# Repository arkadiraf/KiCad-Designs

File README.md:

# KiCad-Designs
KiCad Design Projects

| Project | Description |
|---|---|
| [Pico_Alvik_Adapter](Pico_Alvik_Adapter/) | Raspberry Pi Pico W carrier in Arduino Nano form factor, replaces the Nano ESP32 in the Arduino Alvik robot |
| [Drone_1S_Pico2W](Drone_1S_Pico2W/) | 1S toothpick drone: 2 mm PCB frame / power board (from the OpenSCAD 1S_PiZero frame) and a Pico 2 W flight-controller module. Stage 1: bare boards |
| [PicoBalancer](PicoBalancer/) | Two-wheel self-balancing robot: Pico W / Pico 2 W on sockets, 2 x 18650 (1S2P), BNO086, 2 x MP6550, BQ25606 USB-C charger, TPS61235P 5.1 V boost. Stage 0: outline, datasheets, BOM, design doc |

| [Libraries](Libraries/) | Shared KiCad symbols and footprints for reuse across designs (KD_Power: BQ25606, TPS22997, TPS22810DBV, TPS61235P; KD_Sensors: BMI088, BMP388; KD_Modules: Pico 2 W; KD_Connectors: Bitcraze deck socket; KD_Mechanical: NPTH mounting holes) |

## Ordering (all projects)

One Digi-Key order covers every board: `python Orders/combined_order.py <cart.xlsx> [boards=5]` reads each project's
`fabrication/BOM_DigiKey.csv` (and the Pico_Alvik_Adapter parts list), multiplies by the board count and checks the
cart export, writing `Combined_DigiKey_order.xlsx` next to it (need per project, cart quantity, OK / EXTRA / SHORT /
MISSING / not in any BOM, lines to add, parts bought elsewhere). Order of 28 Nov 2026 (5 of each board, Pico 2 W / Pico W from Mouser): [Orders/2026-11-28/](Orders/2026-11-28/).
Stock passives (0603 R / C sample book, 0805 LEDs) for all boards: `python Orders/stock_passives.py [boards=5]` ->
`Stock_passives.xlsx` (checklist with a Have column) and `Stock_passives.md`.

## Design rules (all projects)

* **Passives:** chip resistors and capacitors are **0603**. Bulk capacitors (10 µF and up, or where the
  voltage rating needs a bigger case) are **0805 or 1206**. No 0402 or smaller: the boards are
  hand-assembled. Exceptions (e.g. a current-sense or power resistor in a larger case) must be
  stated next to the part in the project's `design.py`.
* **LEDs:** 0805 (`LED_SMD:LED_0805_2012Metric`). `Drone_1S_Pico2W/tools/check_bom.py`
  enforces this rule. Copy it into new projects.
* **Shared parts:** custom symbols and footprints go in [Libraries](Libraries/), not project-local
  libraries, so later designs can reuse them.

Workflow for new projects (design-as-code generators, checks, manufacturing outputs): see [AGENTS.md](AGENTS.md).

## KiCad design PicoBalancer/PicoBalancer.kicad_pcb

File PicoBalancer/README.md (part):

# PicoBalancer: two-wheel self-balancing robot board

One 60 × 200 × 1.6 mm PCB for a two-wheel balancing robot:
* **MCU:** Raspberry Pi Pico W (RP2040) on 2 × 20 female sockets, upgradable to a Pico 2 W (RP2350) with no board change.
* **Cells:** plain 2 × 18650 (no protection PCB) in parallel (1S2P) in Keystone 1042 holders (not polarized, Digi-Key 36-1042-ND), or the polarized 1042P on the same footprint. Each cell has its own reverse-polarity FET.
* **IMU:** BNO086 on SPI1.
* **Motors:** 2 × MP6550 H-bridges for Pololu #3072 micro metal gearmotors (30:1 HPCB 6V, extended shaft), each with a Pololu 4761 magnetic encoder on one JST-SH 6-pin connector. ISET 4.3 k caps each motor at 1.16 A.
* **Power:** the blocks are reused from [Drone_1S_Pico2W](../Drone_1S_Pico2W/): BQ25606 USB-C charger (vertical GCT USB4235), TPS22810 Pico switch with UVLO, TPS61235P 5.1 V boost.

**Design document:** [docs/PicoBalancer_Hardware_Design.pdf](docs/PicoBalancer_Hardware_Design.pdf), a PDF export of the shared
design doc (block diagram, circuits, pin map, mechanics, parts list, open decisions).
**PCB order:** [fabrication/PicoBalancer_OSHPark.zip](fabrication/PicoBalancer_OSHPark.zip) (OSH Park 2-layer). See [Fabrication](#fabrication-osh-park-stage-4).
**BOM:**
* [fabrication/BOM.md](fabrication/BOM.md): every line.
* [fabrication/BOM_DigiKey.csv](fabrication/BOM_DigiKey.csv): distributor upload. Digi-Key or Mouser, whichever has stock.
* [fabrication/BOM_stock.md](fabrication/BOM_stock.md): 0603 R/C and 0805 LEDs from stock.
* [fabrication/BOM_to_source.md](fabrication/BOM_to_source.md): lines with no distributor number yet.

**Datasheets and verification:** [Materials/bom_datasheets/README.md](Materials/bom_datasheets/README.md).
**Order check:** `python tools/verify_order.py fabrication/DigiKey_order_2026-11-27T093456.xlsx 5` compares the Digi-Key cart with the BOM. Result for the 27 Nov cart (093456): ORDER OK for 5 boards. The Pico WH comes from Mouser / Piitel. Two cart lines are Pico_Alvik_Adapter parts.

## Status: stage 4, ready to order (rev 0.1)

| Stage | Content | State |
|---|---|---|
| 0 | Folder, datasheets, outline + holes from the DXF (checked against Fusion), placement guides, BOM, design doc | **done** |
| 1 | Decisions closed (motor, cells, TS fixed, UVLO option, placement); follow-up: BAT fuse | done |
| 2 | Netlist in `design.py`, KD symbols/footprints (BNO086, MP6550, Pico socket, 1042, USB4235, slide switch, 1812L, wire pads), schematic | **done** |
| 3 | Placement, silkscreen, routing (2 layers): DRC 0 violations, 0 unconnected | **done** |
| 4 | Final review, OSH Park fab outputs (Gerbers, drill, top stencil, positions) | **done** |

## Mechanics

Sources: `Materials/extracted/PicoBalancer_PCB.dxf` and the Fusion 360 model `PicoBalancer_V01 v2`. The model was
read only, over its local MCP server, and **must not be changed without approval.**

Board coordinates: origin at the board centre, x right, y down, viewed from the holder side. The wheel end is at +y.
Fusion: `y_kicad = 121 - y_fusion`.

| Item | Position (mm) |
|---|---|
| Outline | 60 × 200 |
| Holes | 6 × Ø2.65 NPTH (M2.5) at x ±26, y −96 / 0 / +96, 8 × 8 squares from the DXF and Ø7.5 mm head keep-out marks; 2 clamp holes at (0, −61) / (0, −81) (`KD_Mechanical:MountingHole_2.65mm_NPTH`) |
| BT1 / BT2 (1042, alt. 1042P) | centres (±19.675, −49.975): outer walls on the board edges, top end 11.5 mm from the top edge, + contact at the top end (USB side), − spring toward the board centre; pads ≥ 7.46 × 6.47 mm, ≥ 86.80 mm overall, holes Ø3.45 / Ø2.39 mm |
| Channel between holders | x ±8.65, y −93.5…−6.9: vertical USB-C at the top, BQ25606 charger below, two battery-clamp holes in the middle (positions to come from Fusion) |
| Pico | centred, x ±10.5, y 33…84 (antenna end 2.4 mm above the IMU), micro-USB up |
| IMU | centre bottom, about (0, 89): nearest the wheel axle |
| J7 / J8 motor wire pads | bottom corners, left / right, with U3 / U4 drivers above; motor cables soldered directly |

Fusion findings, reported but not changed:
* The 1042P locating pegs pass through the PCB body.
* The PCB body has no holes for those pegs.

## Placement review in Fusion 360 (stage 0b)

`tools/fusion/build_review.py` builds a `PCB_Review` component in the Fusion model (user permission, 27 Nov 2026) from
`design.py`. It contains a 60 × 200 mm board with all holes and one sized block per part (`REVIEW_PARTS`). It also moves
the two holder models to `BT_POS`. The original `PCB` body is hidden. Rerun it after changing `design.py`:

```sh
cd tools/fusion
python build_review.py                 # needs Fusion running with the PicoBalancer model open (MCP server on :27182)
python fusion_mcp.py view_top.py && python screenshot.py ../../docs/fusion_review_top.png 900 1500
```

* **Bolt keep-out:** Ø7.5 mm circle marked at each M2.5 hole (5 mm head).
* **Holder position:** `HOLDER_TOP_OFFSET` is the distance from the PCB top edge to the housing top end: 11.5 mm (confirmed 27 Nov 2026, also the minimum for the keep-out).
* **Battery clamp:** holes at (0, −61) and (0, −81), with the cover pillar (x ±5, y −86…−56) kept free of parts. The charger sits below the pillar and the USB-C above it.
* **Holder joints:**
  * The left holder is positioned through the offsets of the model's rigid joint "Rigid 6".
  * The right holder is a mirrored copy in the model, so its locating bosses are on the wrong diagonal. The review PCB holes follow a real holder.

## Key electrical choices (details in the design doc)

* **Reverse-polarity protection, one channel per cell** (Q1–Q4, R28–R33). A shared FET cannot protect parallel cells.
  * Each holder's + contact goes to BAT through its own P-FET (DMP2008UFG, 9.8 mΩ max at −2.5 V).
  * A DMG2302U turns that P-FET on only when its own cell is the right way round.
  * A reversed cell is blocked, an empty holder's contacts are dead, and charging still works through the P-FET channel.
  * This makes the non-polarized Keystone 1042 safe to use.
* **Resettable fuse per cell** (F1/F2, Littelfuse 1812L260TH: 2.6 A hold, 5.2 A trip, 8 V) between each holder's + and its P-FET. A short on BAT trips both, and they cap the equalizing current when cells don't match.

* **Back-feed Schottky D2** between the TPS22810 output and Pico VSYS. The Pico's own micro-USB stays usable for
  programming and cannot push current into the cells.
* **Encoder VCC = 3V3.** The Pololu encoder pulls A/B up to its VCC, and RP2040 GPIOs are not 5 V tolerant.
* **BAT feeds both paths:** the TPS22810 (Pico VSYS) and the TPS61235P boost take their input from BAT, after the per-cell FETs. The BQ25606 SYS pin carries only its own capacitors.
* **Boost EN** comes only from the Pico (GP3, 100 k pull-down), so motor power is off by default. MOTOR_EN (GP2) gates
  both MP6550 nSLEEP_HB pins the same way.
* **Charger temperature left out:** TS is held in its normal window by R19 10 k (TH1 not fitted), so charging never stops for temperature.
* **Charging and sleep:** the robot is never driven while charging. It is left switched off to charge slowly. If the power is left on, firmware drops MOTOR_EN and BOOST_EN, sleeps the IMU and sends the Pico dormant. The TPS22810 UVLO is the last backstop: **3.22 V on / 2.65 V off by default** (R21 = 150 k E24 from the sample book, 28 Nov - 156 k gave 3.30 / 2.70 V; R22 = 100 k, R23 = 1.27 M; your choice for plain cells). The internal 2.54 / 2.41 V needs R21 = 0 Ω and R22 / R23 left off. Firmware sleeps well above it.
* **Placement:** boost on the left beside the Pico, above the left driver. Slide switch centred between the Pico and the right board edge, at the micro-USB height, with the Pico power path (TPS22810, D2, power LED) below it.
* **Pin map v2** (`design.PINMAP`, placement-matched): BNO086 on SPI1 (MISO GP12, CS GP13, SCK GP14, MOSI GP11) with RST GP10, INT GP15, WAKE GP22. GP11 and GP15 were swapped on 28 Nov so all four SPI lines reach the Pico in order on the top layer. GP11 is SPI1 TX on both the RP2040 and the RP2350, so firmware sets MOSI = GP11 and INT = GP15. Left motor M1 on GP8/9 with encoder GP6/7; right motor M2 on GP20/21 with encoder GP16/17. MOTOR_EN GP2, BOOST_EN GP3, CHG STAT/PG GP4/5, user LED GP19 (no button), ADC GP26–28. SPI wiring follows the SparkFun breakout v10 (`design.BNO086_PINS`).
* **Slide switch:** NKK AS12AP (non-shorting, 360-2121-ND), the only switch ordered, on the TPS22810 EN/UVLO pin, signal only. Its 0.6 mm pins go into 0.9 mm holes.
  * **Slide up (toward the cells) = ON**, marked ON / OFF on the silkscreen. NKK Series AS: the actuator at the terminal-1 end connects 2-1, and pin 1 goes to BAT through R34.
  * R34 (1 k) stays, so a shorting switch would also work. It adds 0.6 % to the divider top, which shifts the turn-on threshold from 3.30 to about 3.32 V.
* **Motor wiring:** the motor and encoder cables are soldered directly to J7 / J8, two rows of 2 mm pads named GND B A VCC M2 M1 on the silkscreen. Cut a Pololu 4765 cable in half, one half per motor, and solder the wires in color order: pad n = encoder pin n, pin 1 green … pin 6 red. The JST connectors J3/J4 were dropped and are not in the BOM.

## Schematic (stage 2)

`PicoBalancer.kicad_sch` (PDF: [docs/PicoBalancer_Schematic.pdf](docs/PicoBalancer_Schematic.pdf)) is generated from
`build_nets()` in `tools/design.py`. Every pin has a net label, there are no wires between parts, and
`check_netlist.py` compares KiCad's netlist with `design.py`. The sheet has 94 parts and 76 nets.

* **New shared library parts** in `Libraries/tools/gen_lib.py`. Each land pattern is taken from its datasheet; the sources are in the docstrings.
  * Symbols: KD_Sensors:BNO086, KD_Power:MP6550, KD_Modules:RPi_Pico_W_Socket.
  * Footprints: CEVA LGA-28, MPS QFN-12 2×2, Keystone 1042, GCT USB4235 vertical, 3-pin 2.54 mm slide switch, Littelfuse 1812L, 6 named wire pads, Pico 2×20 socket.
* **U1 = the Pico on its sockets.** Its footprint is the two 1×20 socket rows. J1/J2 (the Sullins sockets) are BOM lines only and have no symbol.
* **Wire pads J3W / J4W are renamed J7 / J8.** KiCad needs a reference to end in a number.
* **New part, R36 10k: STAT → CHG_STAT (GP4).** D1 pulls STAT up to SYS, which stays at or below VBAT + 50 mV (about 4.28 V max, SLUSCK6C VSYS).
  * Pico on: GP4 uses its internal pull-up, and D1 stays dark.
  * Pico off while charging: R36 keeps the back-feed into the GPIO under 0.2 mA.
  * CHG_PG (GP5) uses the Pico's internal pull-up.
* **Stock symbols:**
  * Q1/Q2 use Transistor_FET:DMP3013SFV, which has the same PowerDI3333-8 pinout as the DMP2008UFG: S 1-3, G 4, D 5.
  * Q3/Q4 use Transistor_FET:DMG2302U, flattened from Q_NMOS_GSD.
* **Unconnected pins:**
  * Pico: GP0, GP1 and GP18 (spare), RUN, ADC_VREF, 3V3_EN, VBUS. The UART0 debug header J6 was dropped (not needed).
  * Charger U6: NC, and VSET. VSET must float to give 4.208 V, which suits plain 4.20 V cells. A short to GND would set 4.352 V and 5–25 k would set 4.400 V, both of which overcharge. Layout: keep GND copper off pin 12.
  * U7: CT.
  * J5: SBU1/2.
  * BNO086: its NC pins.
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
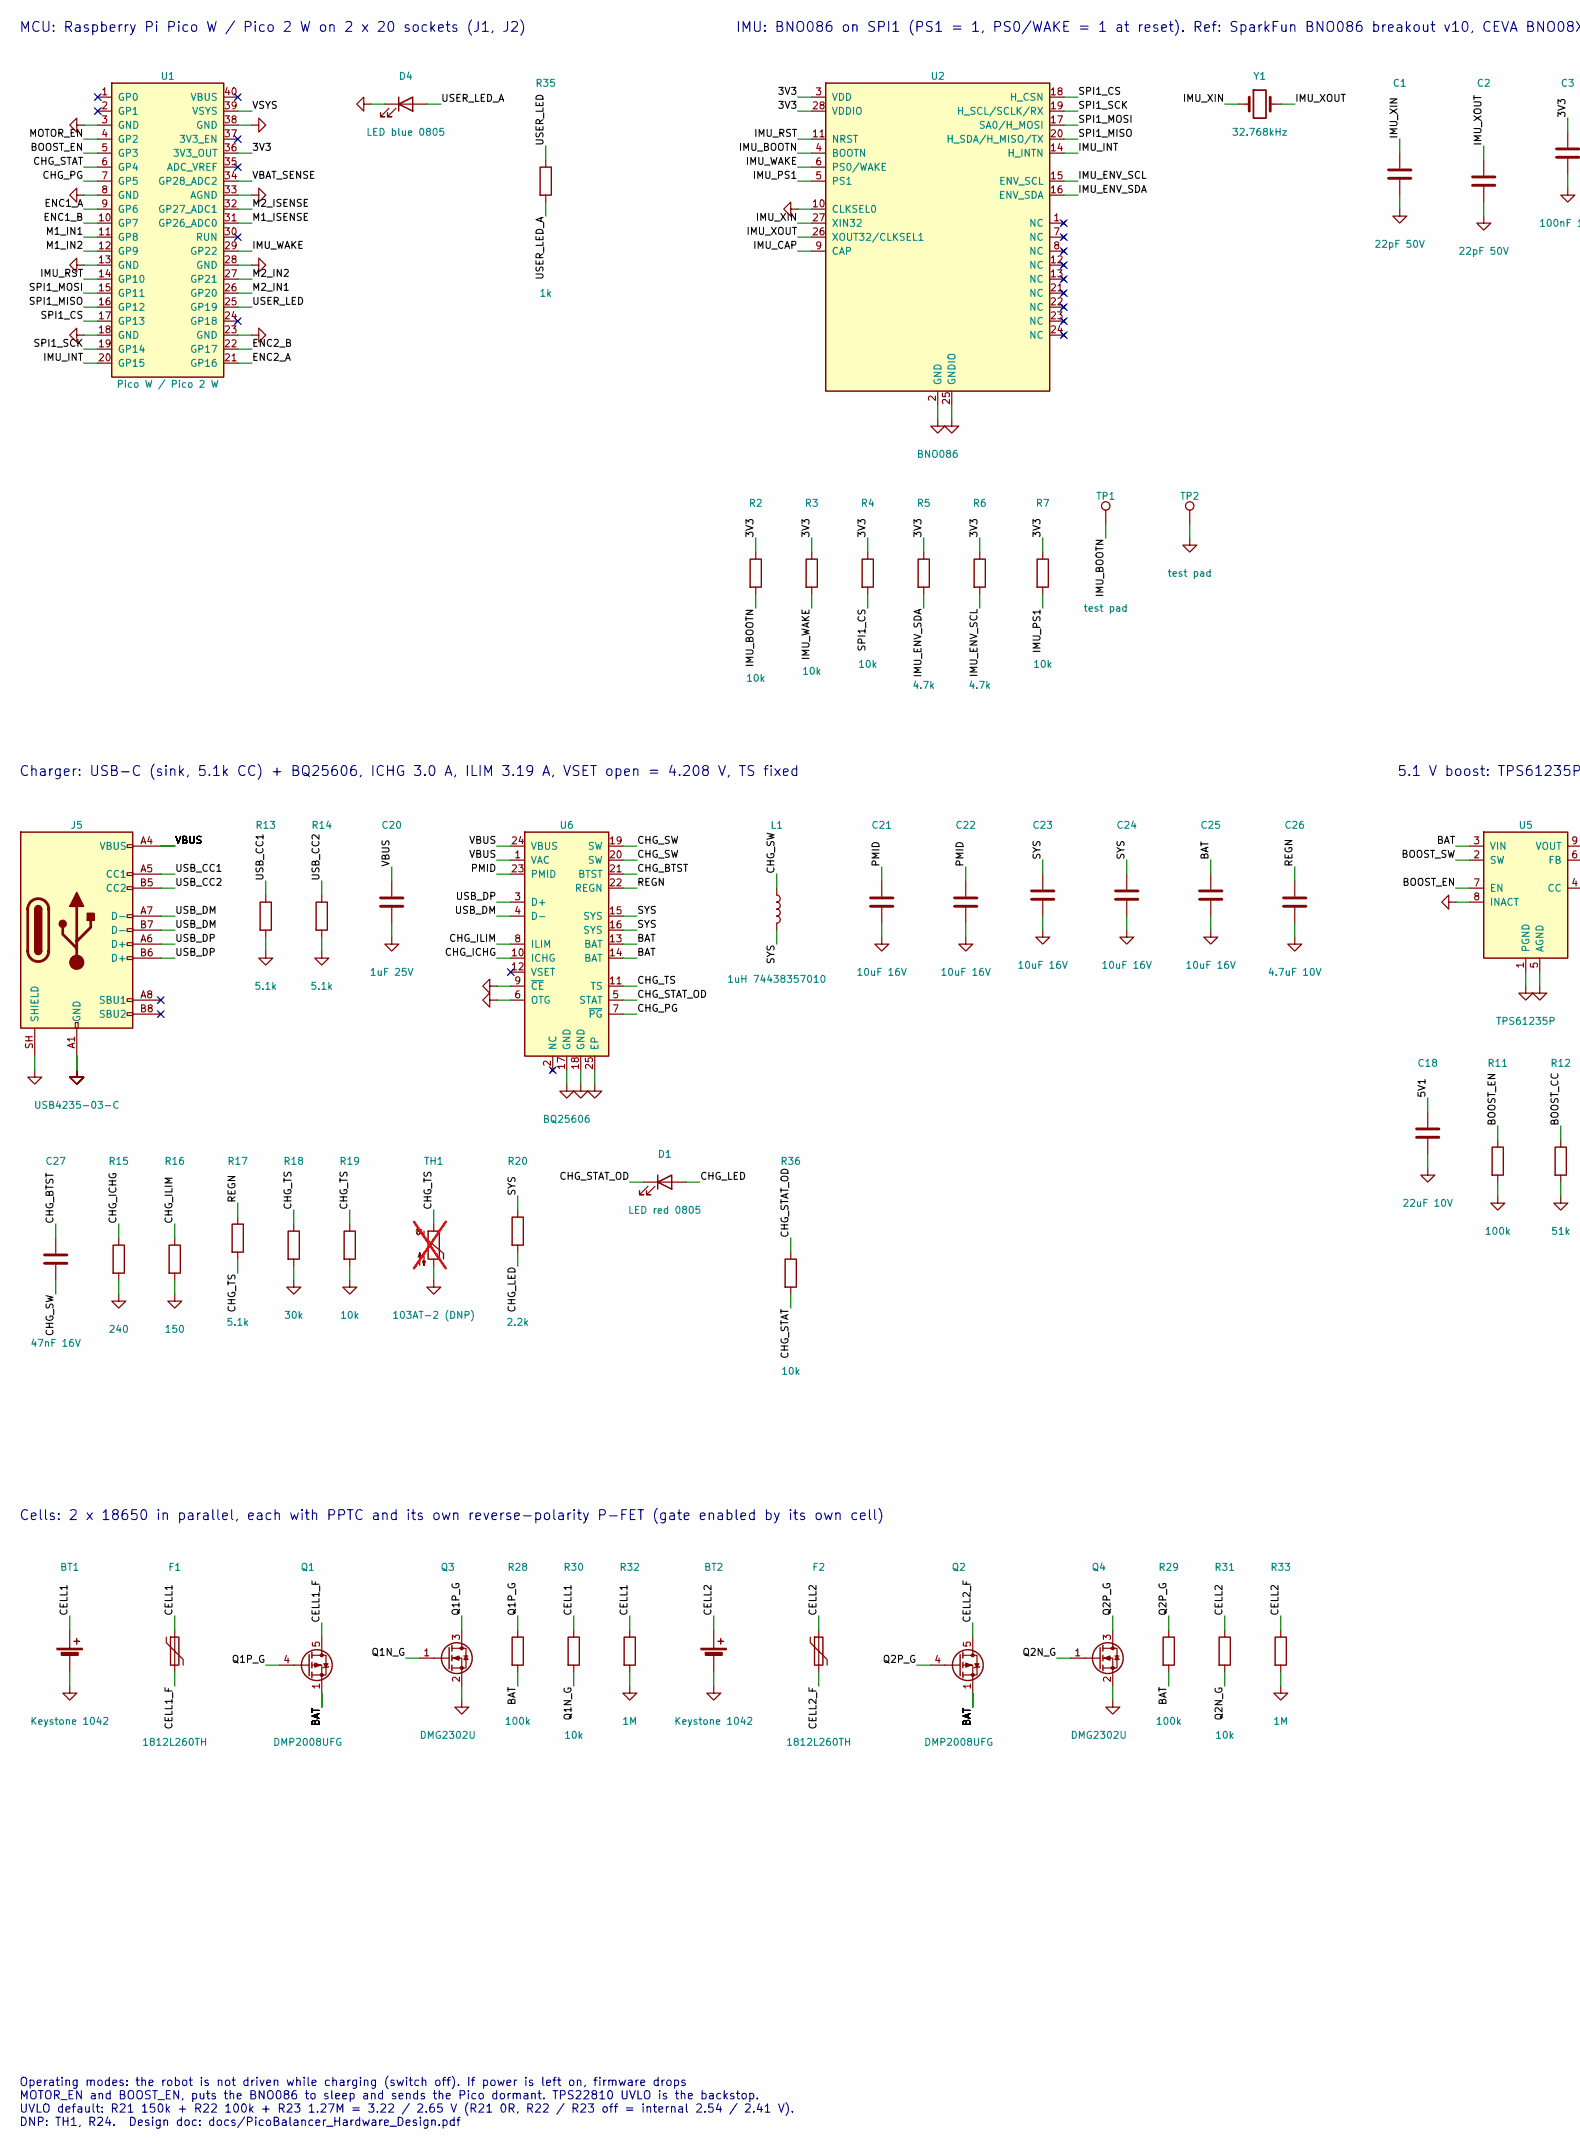
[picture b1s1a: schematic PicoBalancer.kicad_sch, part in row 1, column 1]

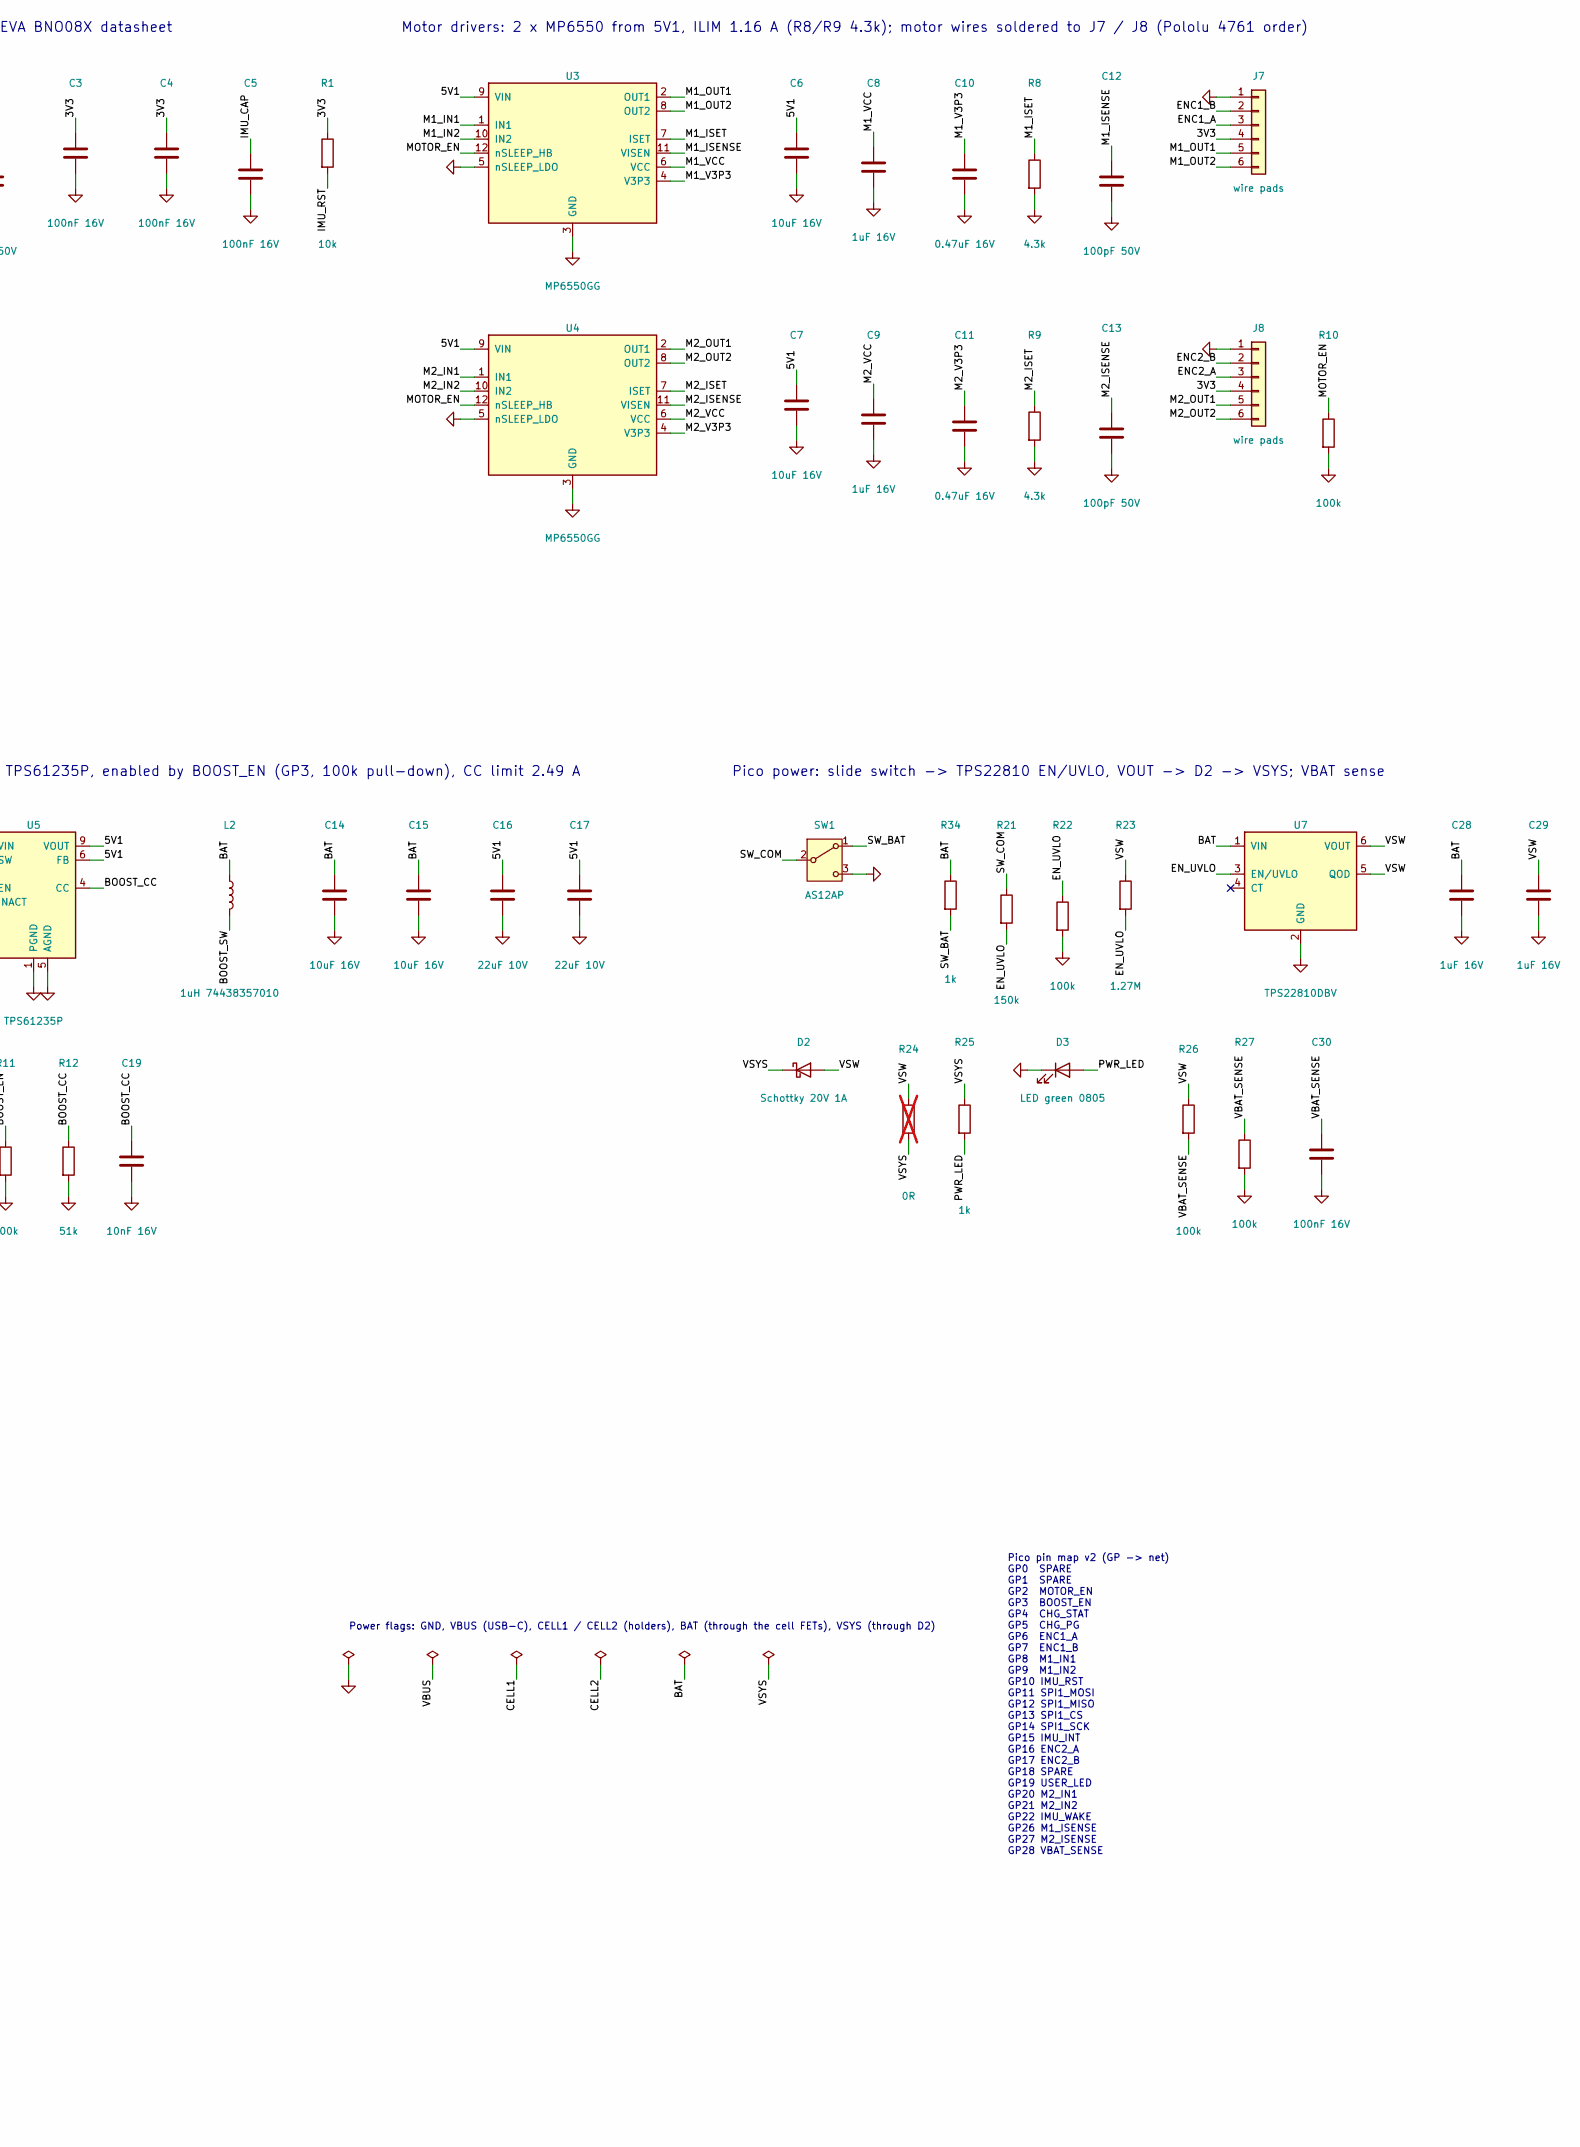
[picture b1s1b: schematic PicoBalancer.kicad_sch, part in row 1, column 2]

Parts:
BT1, BT2: Keystone 1042; Keystone_1042_1x18650_SMD
C1, C2: 22pF 50V; C_0603_1608Metric
C3, C4, C5, C30: 100nF 16V; C_0603_1608Metric
C6, C7, C14, C15, C21, C22, C23, C24, C25: 10uF 16V; C_0805_2012Metric
C8, C9, C28, C29: 1uF 16V; C_0603_1608Metric
C10, C11: 0.47uF 16V; C_0603_1608Metric
C12, C13: 100pF 50V; C_0603_1608Metric
C16, C17, C18: 22uF 10V; C_1206_3216Metric
C19: 10nF 16V; C_0603_1608Metric
C20: 1uF 25V; C_0603_1608Metric
C26: 4.7uF 10V; C_0603_1608Metric
C27: 47nF 16V; C_0603_1608Metric
D1: LED red 0805; LED_0805_2012Metric
D2: Schottky 20V 1A; D_SOD-123F
D3: LED green 0805; LED_0805_2012Metric
D4: LED blue 0805; LED_0805_2012Metric
F1, F2: 1812L260TH; Fuse_Littelfuse_1812L
J5: USB4235-03-C; USB_C_Receptacle_GCT_USB4235_Vertical
J7, J8: wire pads; SolderWire_Pads_1x06_P2.00mm_Named
L1, L2: 1uH 74438357010; L_Wuerth_MAPI-4030
Q1, Q2: DMP2008UFG; Diodes_PowerDI3333-8
Q3, Q4: DMG2302U; SOT-23
R1, R2, R3, R4, R7, R19, R30, R31, R36: 10k; R_0603_1608Metric
R5, R6: 4.7k; R_0603_1608Metric
R8, R9: 4.3k; R_0603_1608Metric
R10, R11, R22, R26, R27, R28, R29: 100k; R_0603_1608Metric
R12: 51k; R_0603_1608Metric
R13, R14, R17: 5.1k; R_0603_1608Metric
R15: 240; R_0603_1608Metric
R16: 150; R_0603_1608Metric
R18: 30k; R_0603_1608Metric
R20: 2.2k; R_0603_1608Metric
R21: 150k; R_0603_1608Metric
R23: 1.27M; R_0603_1608Metric
R24: 0R; R_0603_1608Metric; not fitted
R25, R34, R35: 1k; R_0603_1608Metric
R32, R33: 1M; R_0603_1608Metric
SW1: AS12AP; SW_Slide_SPDT_3pin_P2.54mm_Vertical
TH1: 103AT-2 (DNP); PinHeader_1x02_P2.54mm_Vertical; not fitted
TP1, TP2: test pad; TestPoint_Pad_D1.5mm
U1: Pico W / Pico 2 W; RPi_Pico_Socket_2x20_P2.54mm_Vertical
U2: BNO086; CEVA_LGA-28_3.8x5.2mm_P0.5mm
U3, U4: MP6550GG; MPS_QFN-12_2x2mm_P0.5mm
U5: TPS61235P; Texas_RWL_VQFN-HR-9_2.5x2.5mm_P0.5mm
U6: BQ25606; Texas_RGE0024H_VQFN-24-1EP_4x4mm_P0.5mm_EP2.7x2.7mm
U7: TPS22810DBV; SOT-23-6
Y1: 32.768kHz; Crystal_SMD_3215-2Pin_3.2x1.5mm

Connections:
3V3: C3.1, C4.1, J7.4, J8.4, R1.1, R2.1, R3.1, R4.1, R5.1, R6.1, R7.1, U1.36 (3V3_OUT), U2.3 (VDD), U2.28 (VDDIO)
5V1: C6.1, C7.1, C16.1, C17.1, C18.1, U3.9 (VIN), U4.9 (VIN), U5.6 (FB), U5.9 (VOUT)
BAT: C14.1, C15.1, C25.1, C28.1, L2.1, Q1.1 (S), Q1.2 (S), Q1.3 (S), Q2.1 (S), Q2.2 (S), Q2.3 (S), R28.2, R29.2, R34.1, U5.3 (VIN), U6.13 (BAT), U6.14 (BAT), U7.1 (VIN)
BOOST_CC: C19.1, R12.1, U5.4 (CC)
BOOST_EN: R11.1, U1.5 (GP3), U5.7 (EN)
BOOST_SW: L2.2, U5.2 (SW)
CELL1: BT1.1 (+), F1.1, R30.1, R32.1
CELL1_F: F1.2, Q1.5 (D)
CELL2: BT2.1 (+), F2.1, R31.1, R33.1
CELL2_F: F2.2, Q2.5 (D)
CHG_BTST: C27.1, U6.21 (BTST)
CHG_ICHG: R15.1, U6.10 (ICHG)
CHG_ILIM: R16.1, U6.8 (ILIM)
CHG_LED: D1.2 (A), R20.2
CHG_PG: U1.7 (GP5), U6.7 (~PG)
CHG_STAT: R36.2, U1.6 (GP4)
CHG_STAT_OD: D1.1 (K), R36.1, U6.5 (STAT)
CHG_SW: C27.2, L1.1, U6.19 (SW), U6.20 (SW)
CHG_TS: R17.2, R18.1, R19.1, TH1.1, U6.11 (TS)
ENC1_A: J7.3, U1.9 (GP6)
ENC1_B: J7.2, U1.10 (GP7)
ENC2_A: J8.3, U1.21 (GP16)
ENC2_B: J8.2, U1.22 (GP17)
EN_UVLO: R21.2, R22.1, R23.2, U7.3 (EN/UVLO)
GND: BT1.2 (-), BT2.2 (-), C1.2, C2.2, C3.2, C4.2, C5.2, C6.2, C7.2, C8.2, C9.2, C10.2, C11.2, C12.2, C13.2, C14.2, C15.2, C16.2, C17.2, C18.2, C19.2, C20.2, C21.2, C22.2, C23.2, C24.2, C25.2, C26.2, C28.2, C29.2, C30.2, D3.1 (K), D4.1 (K), J5.A1 (GND), J5.A12 (GND), J5.B1 (GND), J5.B12 (GND), J5.SH (SHIELD), J7.1, J8.1, Q3.2 (S), Q4.2 (S), R8.2, R9.2, R10.2, R11.2, R12.2, R13.2, R14.2, R15.2, R16.2, R18.2, R19.2, R22.2, R27.2, R32.2, R33.2, SW1.3 (C), TH1.2, TP2.1, U1.3 (GND), U1.8 (GND), U1.13 (GND), U1.18 (GND), U1.23 (GND), U1.28 (GND), U1.33 (AGND), U1.38 (GND), U2.2 (GND), U2.10 (CLKSEL0), U2.25 (GNDIO), U3.3 (GND), U3.5 (nSLEEP_LDO), U4.3 (GND), U4.5 (nSLEEP_LDO), U5.1 (PGND), U5.5 (AGND), U5.8 (INACT), U6.6 (OTG), U6.9 (~CE), U6.17 (GND), U6.18 (GND), U6.25 (EP), U7.2 (GND)
IMU_BOOTN: R2.2, TP1.1, U2.4 (BOOTN)
IMU_CAP: C5.1, U2.9 (CAP)
IMU_ENV_SCL: R6.2, U2.15 (ENV_SCL)
IMU_ENV_SDA: R5.2, U2.16 (ENV_SDA)
IMU_INT: U1.20 (GP15), U2.14 (H_INTN)
IMU_PS1: R7.2, U2.5 (PS1)
IMU_RST: R1.2, U1.14 (GP10), U2.11 (NRST)
IMU_WAKE: R3.2, U1.29 (GP22), U2.6 (PS0/WAKE)
IMU_XIN: C1.1, U2.27 (XIN32), Y1.1
IMU_XOUT: C2.1, U2.26 (XOUT32/CLKSEL1), Y1.2
M1_IN1: U1.11 (GP8), U3.1 (IN1)
M1_IN2: U1.12 (GP9), U3.10 (IN2)
M1_ISENSE: C12.1, U1.31 (GP26_ADC0), U3.11 (VISEN)
M1_ISET: R8.1, U3.7 (ISET)
M1_OUT1: J7.5, U3.2 (OUT1)
M1_OUT2: J7.6, U3.8 (OUT2)
M1_V3P3: C10.1, U3.4 (V3P3)
M1_VCC: C8.1, U3.6 (VCC)
M2_IN1: U1.26 (GP20), U4.1 (IN1)
M2_IN2: U1.27 (GP21), U4.10 (IN2)
M2_ISENSE: C13.1, U1.32 (GP27_ADC1), U4.11 (VISEN)
M2_ISET: R9.1, U4.7 (ISET)
M2_OUT1: J8.5, U4.2 (OUT1)
M2_OUT2: J8.6, U4.8 (OUT2)
M2_V3P3: C11.1, U4.4 (V3P3)
M2_VCC: C9.1, U4.6 (VCC)
MOTOR_EN: R10.1, U1.4 (GP2), U3.12 (nSLEEP_HB), U4.12 (nSLEEP_HB)
PMID: C21.1, C22.1, U6.23 (PMID)
PWR_LED: D3.2 (A), R25.2
Q1N_G: Q3.1 (G), R30.2
Q1P_G: Q1.4 (G), Q3.3 (D), R28.1
Q2N_G: Q4.1 (G), R31.2
Q2P_G: Q2.4 (G), Q4.3 (D), R29.1
REGN: C26.1, R17.1, U6.22 (REGN)
SPI1_CS: R4.2, U1.17 (GP13), U2.18 (H_CSN)
SPI1_MISO: U1.16 (GP12), U2.20 (H_SDA/H_MISO/TX)
SPI1_MOSI: U1.15 (GP11), U2.17 (SA0/H_MOSI)
SPI1_SCK: U1.19 (GP14), U2.19 (H_SCL/SCLK/RX)
SW_BAT: R34.2, SW1.1 (A)
SW_COM: R21.1, SW1.2 (B)
SYS: C23.1, C24.1, L1.2, R20.1, U6.15 (SYS), U6.16 (SYS)
USB_CC1: J5.A5 (CC1), R13.1
USB_CC2: J5.B5 (CC2), R14.1
USB_DM: J5.A7 (D-), J5.B7 (D-), U6.4 (D-)
USB_DP: J5.A6 (D+), J5.B6 (D+), U6.3 (D+)
USER_LED: R35.1, U1.25 (GP19)
USER_LED_A: D4.2 (A), R35.2
VBAT_SENSE: C30.1, R26.2, R27.1, U1.34 (GP28_ADC2)
VBUS: C20.1, J5.A4 (VBUS), J5.A9 (VBUS), J5.B4 (VBUS), J5.B9 (VBUS), U6.1 (VAC), U6.24 (VBUS)
VSW: C29.1, D2.2 (A), R23.1, R24.1, R26.1, U7.5 (QOD), U7.6 (VOUT)
VSYS: D2.1 (K), R24.2, R25.1, U1.39 (VSYS)

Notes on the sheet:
MCU: Raspberry Pi Pico W / Pico 2 W on 2 x 20 sockets (J1, J2)
IMU: BNO086 on SPI1 (PS1 = 1, PS0/WAKE = 1 at reset). Ref: SparkFun BNO086 breakout v10, CEVA BNO08X datasheet
Motor drivers: 2 x MP6550 from 5V1, ILIM 1.16 A (R8/R9 4.3k); motor wires soldered to J7 / J8 (Pololu 4761 order)
Charger: USB-C (sink, 5.1k CC) + BQ25606, ICHG 3.0 A, ILIM 3.19 A, VSET open = 4.208 V, TS fixed
5.1 V boost: TPS61235P, enabled by BOOST_EN (GP3, 100k pull-down), CC limit 2.49 A
Pico power: slide switch -> TPS22810 EN/UVLO, VOUT -> D2 -> VSYS; VBAT sense
Cells: 2 x 18650 in parallel, each with PPTC and its own reverse-polarity P-FET (gate enabled by its own cell)
Power flags: GND, VBUS (USB-C), CELL1 / CELL2 (holders), BAT (through the cell FETs), VSYS (through D2)
Pico pin map v2 (GP -> net) GP0 SPARE GP1 SPARE GP2 MOTOR_EN GP3 BOOST_EN GP4 CHG_STAT GP5 CHG_PG GP6 ENC1_A GP7 ENC1_B GP8 M1_IN1 GP9 M1_IN2 GP10 IMU_RST GP11 SPI1_MOSI GP12 SPI1_MISO GP13 SPI1_CS GP14 SPI1_SCK GP15 IMU_INT GP16 ENC2_A GP17 ENC2_B GP18 SPARE GP19 USER_LED GP20 M2_IN1 GP21 M2_IN2 G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
Operating modes: the robot is not driven while charging (switch off). If power is left on, firmware drops MOTOR_EN and BOOST_EN, puts the BNO086 to sleep and sends the Pico dormant. TPS22810 UVLO is the backstop. UVLO default: R21 150k + R22 100k + R23 1.27M = 3.22 / 2.65 V (R21 0R, R22 / R23 off =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

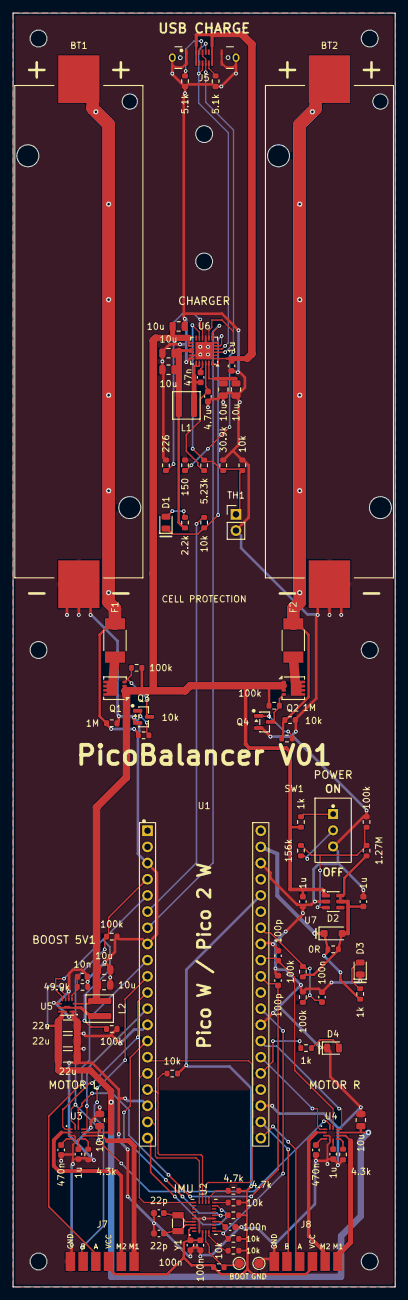
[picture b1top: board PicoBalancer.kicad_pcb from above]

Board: 2 copper layers, 60.0 x 200.0 mm, 103 parts (0 on the bottom side), 76 nets.

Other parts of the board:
H1, H2, H3, H4, H5, H6, H7, H8: MountingHole_2.65mm_NPTH

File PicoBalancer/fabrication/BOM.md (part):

# BOM - PicoBalancer (one board)

Generated by tools/export_bom.py from design.py + parts.py. Supply: Digi-Key or Mouser, whichever has stock. Stock = 0603 R / C sample book and 0805 LEDs.

| Refs | Qty | Part | Footprint | Manufacturer | MPN | Digi-Key PN | Status | Note |
|---|---|---|---|---|---|---|---|---|
| U1 | 1 | Raspberry Pi Pico W / Pico 2 W | RPi_Pico_Socket_2x20_P2.54mm_Vertical | Raspberry Pi | `SC0919` | `2648-SC0919-ND` | ok | MCU; the footprint is the two socket rows J1/J2 (2 x 20 pads, rows 17.78 mm); Pico WH (headers fitted) for the sockets; SC0918 = Pico W without headers; Pico 2 WH later; ordered from Mouser / Piitel (user, 2026-11-27), not Digi-Key |
| J1 J2 | 2 | 1x20 female 2.54 mm | (soldered into the U1 footprint) | Sullins | `PPPC201LFBN-RC` | `S7053-ND` | ok | Pico sockets, rows 17.78 mm apart; bought parts, no schematic symbol of their own; 1x20 female 2.54 mm, 8.50 mm insulator |
| U2 | 1 | BNO086 | CEVA_LGA-28_3.8x5.2mm_P0.5mm | CEVA | `BNO086` | `1888-BNO086CT-ND` | ok | 9-axis IMU with fusion, SPI1 (PS1 high, PS0/WAKE high at reset); LGA-28 |
| Y1 | 1 | 32.768kHz 12.5pF | Crystal_SMD_3215-2Pin_3.2x1.5mm | Epson | `FC-135 32.7680KA-A5` | `SER4103CT-ND` | ok | BNO086 XIN32 / XOUT32; 32.768 kHz, 12.5 pF, +-20 ppm (ordered, Digi-Key SER4103CT-ND) |
| C1 C2 | 2 | 22pF 50V | C_0603_1608Metric | Murata | `GRM1885C1H220JA01D` | — | stock | crystal load (check vs crystal CL); 22 pF C0G 0603 (stock) |
| C3 C4 C5 | 3 | 100nF 16V | C_0603_1608Metric | Samsung | `CL10B104KB8NNNC` | — | stock | BNO086 VDD, VDDIO, CAP; 100 nF 50 V X7R 0603 (stock); replaces GRM188R71H104KA93D (EOL at distributors) |
| R1 R2 | 2 | 10k | R_0603_1608Metric | Yageo | `RC0603FR-0710KL` | — | stock | BNO086 NRST / BOOTN pull-ups |
| R3 R4 | 2 | 10k | R_0603_1608Metric | Yageo | `RC0603FR-0710KL` | — | stock | BNO086 PS0/WAKE and H_CSN pull-ups (SPI select at reset, CS idle high) |
| R5 R6 | 2 | 4.7k | R_0603_1608Metric | Yageo | `RC0603FR-074K7L` | — | stock | BNO086 S_SDA / S_SCL pull-ups (sensor bus, unused) |
| R7 | 1 | 10k | R_0603_1608Metric | Yageo | `RC0603FR-0710KL` | — | stock | BNO086 PS1 pull-up (SPI mode) |
| U3 U4 | 2 | MP6550GG | MPS_QFN-12_2x2mm_P0.5mm | Monolithic Power Systems | `MP6550GG-Z` | `1589-MP6550GG-ZCT-ND` | ok | H-bridge per motor, 5V1 supply; QFN-12 2 x 2 mm |
| C6 C7 | 2 | 10uF 16V | C_0805_2012Metric | Murata | `GRM21BR61E106KA73L` | `490-5523-1-ND` | ok | MP6550 VIN, at the pin; 10 uF 25 V X5R 0805 (ordered; replaces GRM21BR61C106KE15L) |
| C8 C9 | 2 | 1uF 16V | C_0603_1608Metric | Samsung | `CL10B105KA8NNNC` | — | stock | MP6550 VCC bypass; 1 uF 0603 (stock) |
| C10 C11 | 2 | 0.47uF 16V | C_0603_1608Metric | Samsung | `CL10B474KA8NNNC` | — | stock | MP6550 V3P3 (LDO unused, nSLEEP_LDO = GND); 0.47 uF 0603 (stock) |
| R8 R9 | 2 | 4.3k | R_0603_1608Metric | Yageo | `RC0603FR-074K3L` | — | stock | MP6550 ISET: current limit 1.16 A per motor (both stalled 2.33 A < boost 2.49 A); ISET 1.16 A for the Pololu 3072 (30:1 HPCB 6V) |
| C12 C13 | 2 | 100pF 50V | C_0603_1608Metric | Murata | `GRM1885C1H101JA01D` | — | stock | MP6550 VISEN filter (<= 500 pF), placed at the Pico ADC pins GP26 / GP27; 100 pF C0G 0603 (stock) |
| R10 | 1 | 100k | R_0603_1608Metric | Yageo | `RC0603FR-07100KL` | — | stock | MOTOR_EN (both nSLEEP_HB) pull-down |
| J7 J8 | 2 | 6 solder pads, 2.0 mm pitch (no part) | SolderWire_Pads_1x06_P2.00mm_Named | - | `pads only` | — | ok | motor + encoder wires soldered directly (Pololu 4761 order: GND, B, A, VCC=3V3, M2, M1), silk names; 2 mm solder pads for direct wiring |
| U5 | 1 | TPS61235P | Texas_RWL_VQFN-HR-9_2.5x2.5mm_P0.5mm | Texas Instruments | `TPS61235PRWLR` | `296-47376-1-ND` | ok | 5V1 for the motor drivers; ordered as the R reel variant (same part as RWLT) |
| L2 | 1 | 1uH, Isat 6.2 A (Wurth 74438357010) | L_Wuerth_MAPI-4030 | Wurth Elektronik | `74438357010` | `732-11197-1-ND` | ok | boost inductor |
| C14 C15 | 2 | 10uF 16V | C_0805_2012Metric | Murata | `GRM21BR61E106KA73L` | `490-5523-1-ND` | ok | boost input, on BAT (user 2026-11-27) |
| C16 C17 C18 | 3 | 22uF 10V | C_1206_3216Metric | Samsung | `CL31B226KPHNFNE` | `1276-3145-1-ND` | ok | boost output, >= 20 uF effective at 5.1 V; 22 uF 10 V X7R 1206 |
| R11 | 1 | 100k | R_0603_1608Metric | Yageo | `RC0603FR-07100KL` | — | stock | BOOST_EN pull-down |
| R12 | 1 | 51k | R_0603_1608Metric | Yageo | `RC0603FR-0751KL` | — | stock | boost CC limit 2.44 A (E24; 49.9k = 2.49 A); E24 (sample book, user 2026-11-28): 2.44 A |
| C19 | 1 | 10nF 16V | C_0603_1608Metric | Samsung | `CL10B103KB8NNNC` | — | stock | CC pin, parallel to R12; 10 nF 50 V X7R 0603 (stock); replaces GRM188R71H103KA01D (EOL) |
| J5 | 1 | USB-C receptacle vertical (GCT USB4235-03-C) | USB_C_Receptacle_GCT_USB4235_Vertical | GCT | `USB4235-03-C` | `2073-USB4235-03-CCT-ND` | ok | charge input, D+/D- to the charger; vertical SMT, 6.5 mm; land pattern from GCT drawing sheet 2; fallback USB4120-03-C |
| U6 | 1 | BQ25606 | Texas_RGE0024H_VQFN-24-1EP_4x4mm_P0.5mm_EP2.7x2.7mm | Texas Instruments | `BQ25606RGER` | `296-47743-1-ND` | ok | 1S 3 A charger, power path (thermal vias 0.3 mm added at routing: the stock _ThermalVias variant uses 0.2 mm drills) |
| L1 | 1 | 1uH, Isat 6.2 A (Wurth 74438357010) | L_Wuerth_MAPI-4030 | Wurth Elektronik | `74438357010` | `732-11197-1-ND` | ok | charger buck inductor |
| R13 R14 | 2 | 5.1k | R_0603_1608Metric | Yageo | `RC0603FR-075K1L` | — | stock | USB-C CC1 / CC2 pull-downs |
| R15 | 1 | 240 | R_0603_1608Metric | Yageo | `RC0603FR-07240RL` | — | stock | ICHG 2.82 A (1.41 A per cell; E24, 226 = 3.0 A); E24 (sample book, user 2026-11-28): ICHG 2.82 A |
| R16 | 1 | 150 | R_0603_1608Metric | Yageo | `RC0603FR-07150RL` | — | stock | ILIM 3.19 A |
| R17 | 1 | 5.1k | R_0603_1608Metric | Yageo | `RC0603FR-075K1L` | — | stock | TS divider top (E24; 2-61 C with an NTC); E24 (sample book, user 2026-11-28) |
| R18 | 1 | 30k | R_0603_1608Metric | Yageo | `RC0603FR-0730KL` | — | stock | TS divider bottom (E24); E24 (sample book, user 2026-11-28) |
| TH1 | 0 | 10k NTC 103AT-2 | PinHeader_1x02_P2.54mm_Vertical | Semitec | `103AT-2` | `4316-103AT-2-ND` | DNP | cell temperature (DNP: charger temperature left out, user 2026-11-27); charger temperature left out (user 2026-11-27); R19 fitted instead; bulk |
| R19 | 1 | 10k | R_0603_1608Metric | Yageo | `RC0603FR-0710KL` | — | stock | fixed TS resistor in place of TH1 (charger temperature left out); fixed TS: 30k parallel 10k, with 5.1k -> TS = 0.595 REGN (normal window, ~25 C) |
| C20 | 1 | 1uF 25V | C_0603_1608Metric | Samsung | `CL10B105KA8NNNC` | — | stock | VBUS; 1 uF 25 V 0603 (stock) |
| C21 C22 | 2 | 10uF 16V | C_0805_2012Metric | Murata | `GRM21BR61E106KA73L` | `490-5523-1-ND` | ok | PMID |
| C23 C24 | 2 | 10uF 16V | C_0805_2012Metric | Murata | `GRM21BR61E106KA73L` | `490-5523-1-ND` | ok | SYS (only load on SYS: <= 20 uF per datasheet) |
| C25 | 1 | 10uF 16V | C_0805_2012Metric | Murata | `GRM21BR61E106KA73L` | `490-5523-1-ND` | ok | BAT |
| C26 | 1 | 4.7uF 10V | C_0603_1608Metric | Murata | `GRM188R61A475KAAJD` | — | stock | REGN; 4.7 uF 10 V X5R 0603 (stock); Digi-Key upgrade of the obsolete GRM188R61A475KE15D |
| C27 | 1 | 47nF 16V | C_0603_1608Metric | Samsung | `CL10B473KB8NNNC` | — | stock | BTST; 47 nF 50 V X7R 0603 (stock); replaces GRM188R71H473KA61D (not found at Digi-Key) |
| D1 | 1 | LED red 0805 | LED_0805_2012Metric | Lite-On | `LTST-C171KRKT` | — | stock | STAT charging, from SYS (TI application diagram); red 0805 (stock) |
| R36 | 1 | 10k | R_0603_1608Metric | Yageo | `RC0603FR-0710KL` | — | stock | STAT -> CHG_STAT (GP4) series resistor; CHG_STAT series |
| R20 | 1 | 2.2k | R_0603_1608Metric | Yageo | `RC0603FR-072K2L` | — | stock | STAT LED series |
| U7 | 1 | TPS22810DBV | SOT-23-6 | Texas Instruments | `TPS22810DBVT` | `296-45304-1-ND` | ok | Pico VSYS switch, input BAT (user 2026-11-27), UVLO 3.30 / 2.70 V (divider R21-R23); ordered as DBVT (small reel), same part as DBVR |
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
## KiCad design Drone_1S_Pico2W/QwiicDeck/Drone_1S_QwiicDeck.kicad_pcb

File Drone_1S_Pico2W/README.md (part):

# Drone_1S_Pico2W: electronics for the 1S toothpick drone

Two boards for the 140 mm, single-18650 quad in
[OpenScad-Designs/Drones/1S_PiZero](https://github.com/arkadiraf/OpenScad-Designs/tree/main/Drones/1S_PiZero).
The flight controller is a **Raspberry Pi Pico 2 W** (RP2350 + CYW43439) on a new, custom module board.
It replaces the Crazyflie Bolt of the OpenSCAD design.

**The FC module leads the design and the frame follows it.** The OpenSCAD frame was drawn for the
Bolt, so the imported frame is only a mechanical baseline (outline, motor and ESC positions). Its
FC holes, connectors and wiring will be redone to suit the new FC and the 2 × 10 interface.

The design intent comes from
[Materials/Toothpick_Drone_Hardware_Design_1S_Pico_2_W.pdf](Materials/Toothpick_Drone_Hardware_Design_1S_Pico_2_W.pdf)
(2026-11-25). Its text is in `Materials/extracted/design_doc.txt`.

| Board | Folder | Size | Thickness | Carries |
|---|---|---|---|---|
| **Frame** (power board) | [Frame/](Frame/) | 117 × 117 mm, the quad frame itself | **2.0 mm** | 18650 tab pads, USB-C + BQ25606 charger, TPS22810 Pico rail switch + SPDT slide switch, 4 × TPS22997 motor switches, TPS61235P 5.1 V boost (optional), 4 × DYS XSD7A ESCs on pin headers, Pi Zero 5.1 V output, 2 × 10 header to the FC |
| **FC** (flight controller module) | [FC/](FC/) | 55.3 × 41.5 mm bbox, minimum outline | 1.6 mm | **Top:** Pico 2 W only (castellated SMD, faces the frame). **Bottom:** BMI088 IMU (SPI0), BMP388 baro (I2C0), support ICs, and the Crazyflie deck connectors for the Flow deck v2 (SPI1 + I2C0), which plugs in from below as it does under a Crazyflie. Also JST-SH 4 to the Pi Zero and the 2 × 10 header to the frame |

## Status: stage 1, bare boards (V01; 28 Nov update: orderable B2B connectors, printed-spacer stack, B3U-1000PM-B)

**Design document (PDF, 27 Nov 2026):** [docs/Toothpick_Drone_Hardware_Design_1S_Pico2W.pdf](docs/Toothpick_Drone_Hardware_Design_1S_Pico2W.pdf),
exported from the shared design doc. It has the design status, renders, the parts list and the to-do list.
**Orderable BOM:** [fabrication/BOM.md](fabrication/BOM.md) and
[fabrication/BOM_DigiKey.csv](fabrication/BOM_DigiKey.csv) (upload to the Digi-Key BOM Manager; MPNs are not
yet checked for stock).
**FC order sheet:** [fabrication/BOM_FC.xlsx](fabrication/BOM_FC.xlsx), the flight-controller parts plus the frame's mating
sockets J5/J6, the FC standoffs and the SWD cable, for 5 modules (`export_bom.py`). Connector selection and the
options not taken: [Materials/connector_options/](Materials/connector_options/README.md).
**Frame order sheet:** [fabrication/BOM_Frame.xlsx](fabrication/BOM_Frame.xlsx), for 3 frames (OSH Park ships in
threes; `FRAME_ORDER_BOARDS` in `export_bom.py`): sheet *Order* (every frame line: electrical parts, ESC seats, J5/J6,
J7/J8, cable housings and crimps, frame hardware, with source), *Digi-Key cart* (one line per Digi-Key PN, quantities
summed, no spares) and *Stock* (sample-book values). J5/J6 also appear in the FC sheet: order them once.
**Stock parts** (0603 resistors and capacitors from the sample book, 0805 LEDs): [fabrication/BOM_stock.md](fabrication/BOM_stock.md)
(22 values, with E24 fallbacks for the E96 values); they are left out of the Digi-Key CSV.
**Frame BOM review** (shared libraries, PicoBalancer lessons, decisions of 28 Nov): [Materials/FRAME_BOM_REVIEW.md](Materials/FRAME_BOM_REVIEW.md).
**Still to source** (cables, standoffs, screws, inserts, Samtec parts): [fabrication/BOM_to_source.md](fabrication/BOM_to_source.md).

| Stage | Content | State |
|---|---|---|
| 1 | Outlines, holes, fixed pads, placement guides, design rules | **done** |
| 2 | Pin map and netlist: FC in `tools/fc_design.py`, 2 × 10 header pinout in `design.py` (shared by both boards) | **FC done** (frame: next) |
| 3 | Symbols/footprints, schematics | **FC done** (`FC/Drone_1S_FC.kicad_sch`, NETLIST OK); frame next |
| 3b | 3D review of components and placement (OpenSCAD) | in review (scad not yet updated for the 7 mm stack) |
| 4 | Routing, pours, DRC, fab outputs (see `../AGENTS.md`) | **FC done** (28 Nov 2026, see "FC routing" below); frame next |

Guides: **Dwgs.User** shows top-side parts (props, cell, Pi Zero, Pico). **Cmts.User** shows
bottom-side parts (FC module outline on the frame, Crazyflie deck rows on the FC). Edit them freely.
They don't go to the fab.

### Frame: imported from OpenSCAD

Source: `1S_PiZero.scad`, `part="pcb_outline"`, exported as `1S_PiZero_PCB_outline.dxf` (OpenScad-Designs
commit `115559d`). A copy is in `Materials/extracted/`. The committed DXF was checked against a fresh
OpenSCAD export of the same scad file: same 60 holes, same outline.

`tools/dxf_import.py` takes the largest contour as the outline (312 segments on Edge.Cuts). It fits every
other contour as a circle and snaps it to a known drill:

| Drill | Count | Became | Ref |
|---|---|---|---|
| 4.0 | 4 | motor shaft clearance, NPTH | H1–H4 (with the motor screws) |
| 2.2 | 16 | motor M2 screws, 9 mm PCD, NPTH | H1–H4 (`MotorMount_1203_M2_9mm`) |
| 2.2 | 4 | the shared M2 holes: battery cover + landing gear + FC standoffs, NPTH | H_CV1–4 |
| 1.0 | 28 | ESC header pins, **plated**, 1.7 mm pads | J1–J4: pads 1–4 inner row (power end), 5–7 outer row (motor phases) |
| 0.75 | 2 | JST-PH holes for the Pi 5.1 V connector (JST ePH drill) | J8 (`JST_PH_B2B-PH-K_1x02_P2.00mm_Vertical`), pads asserted on the holes |

Plus **BT1**, the two 3 × 10 mm battery tab pads on top copper at x = ±33.6 mm (from `pcb()` in the
scad). Polarity is not set yet.

`tools/check_import.py` checks every drilled hole in the board against the DXF (within 0.01 mm, same
drill) and checks the outline segment count. Result: `IMPORT OK`, 58 holes.

Motor and ESC names: FL, FR, RR, RL (x forward to the camera, y left). In KiCad the front points right.

### Board-to-board: plug-in FC on standoffs

The FC module sits **under the frame** (the frame top over the centre carries the 18650 and its
cover). It **plugs into the frame through male/female headers**. Nothing is soldered between the
boards, so the FC can be pulled off and replaced.

**The battery cover and the FC share four M2 holes** at (±24, ±17.5). The printed battery cover
also carries the Pi Zero 2 W posts. One M2 × 20 through-bolt per hole (decided 28 Nov 2026), top to bottom:

| Layer | Thickness | |
|---|---|---|
| M2 × 20 galvanized screw ([4project](https://www.4project.co.il/product/screw-m2x20mm-galvanized)), head on the cover boss | | through everything below |
| printed battery cover boss + rail | 4 mm | |
| frame PCB | 2.0 mm | H_CV1–4 |
| **3D-printed spacer**, OD 5 mm, hole 2.3 mm, PETG or ASA (not PLA: creep, softens ~55 °C) | **7.0 mm** | print 7.0–7.2 mm, never under 6.9 mm: the headers seat at 6.6 mm (up to ~6.85 mm at tolerance) |
| FC module | 1.6 mm | H1–H4 (ears) |
| M2 nylon-insert lock nut (DIN 985) | ~2.8 mm | 14.6 mm grip; about 2.6 mm of the screw left for the nut |

Removing the four nuts frees the FC; the cover is then held only by the bolt heads, so keep the drone upright
or take the cover off with it.

**The landing gear has its own four M2 holes** (H_LG1–4) at (±35, ±18.5), near the front and rear
ends of the centre plate and outside the cover rails, so it swaps without touching the cover or the
FC. It is two identical printed skids (front, rear). Each skid is a cross-beam with an M2 heat-set
insert boss and a leg at each end, held by M2 × 4 screws from the frame top. A one-piece frame would
run into the FC standoffs at y = ±17.5. The frame's old 30.5 mm FC holes are gone.

**Connector choice (V01, updated 28 Nov 2026): orderable 2.00 mm pair on 7 mm printed spacers.** Options and
datasheets: [Materials/connector_options/](Materials/connector_options/README.md).
* **What sets the height:** the Pico 2 W's micro-USB is its tallest part, **3.73 mm** above the FC
  (KiCad-RP-Pico 3D model; BOOTSEL 2.08 mm, everything else ≤ 1.68 mm), so the gap must be over ~4 mm.
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
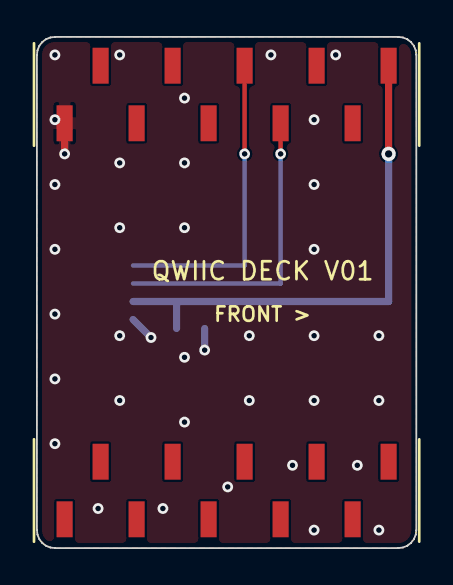
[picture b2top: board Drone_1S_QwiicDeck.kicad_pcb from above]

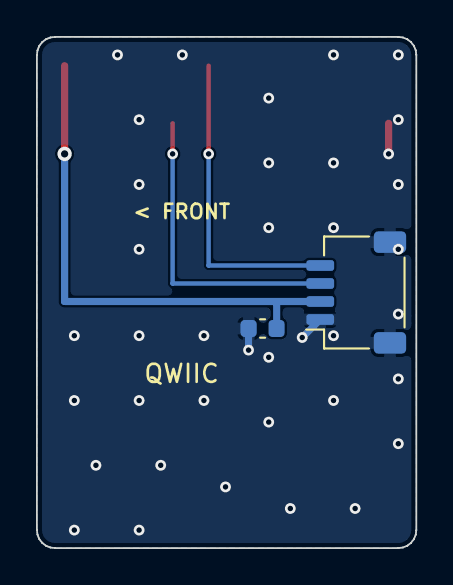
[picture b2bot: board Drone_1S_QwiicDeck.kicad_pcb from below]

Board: 2 copper layers, 21.1 x 28.4 mm, 4 parts (2 on the bottom side), 4 nets.

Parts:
C1: 1u; C_0603_1608Metric
J1: Sullins NPPN101BFLD-RC (FC P1); Sullins_NPPN101BFLD_1x10_P2.00mm_SMD
J2: Sullins NPPN101BFLD-RC (FC P2); Sullins_NPPN101BFLD_1x10_P2.00mm_SMD
J3: Qwiic; JST_SH_SM04B-SRSS-TB_1x04-1MP_P1.00mm_Horizontal

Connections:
3V3: C1.1, J1.1, J3.2
GND: C1.2, J1.10, J3.1, J3.MP
I2C_SCL: J1.5, J3.4
I2C_SDA: J1.4, J3.3

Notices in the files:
Drone_1S_Pico2W/README.md:
exactly these sensors, so their open schematics (bitcraze/hardware, CC-BY-NC-SA 4.0) are the
Bitcraze publishes the Crazyflie flight firmware (GPL-3.0). It already has drivers for the BMI088,
PicoBalancer/tools/design.py:
(Materials/extracted/sparkfun_bno086/, CC BY-SA 4.0) and the CEVA BNO08X datasheet. SparkFun selects SPI with
--- IMU: BNO086, reference = SparkFun BNO086 breakout (CC BY-SA 4.0) + CEVA BNO08X datasheet ---
